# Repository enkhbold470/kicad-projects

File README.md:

# KiCad projects

Five boards, each designed end to end in KiCad 10 and checked by KiCad itself: schematic, ERC, netlist round
trip, placement, routing, pours, silkscreen, DRC with schematic parity, DFM and fab outputs. Each folder holds
the KiCad project, the gerbers / BOM / pick-and-place / STEP, raytraced renders and a video of the design
being built step by step.

<table>
<tr><td align="center" width="50%"><br><b><a href="iron-node/">Iron Node</a></b><br><sub>An ESP32-S3 industrial gateway with Ethernet, isolated RS-485, CAN and a 9-36 V input.</sub></td><td align="center" width="50%"><br><b><a href="pd-brick/">PD Brick</a></b><br><sub>A USB-C Power Delivery bench supply: STUSB4500 sink, LM5176 buck-boost, 1.2-22 V set over I2C by an ESP32-S3.</sub></td></tr>
<tr><td align="center" width="50%"><br><b><a href="probelab/">ProbeLab</a></b><br><sub>An RP2040 USB-C logic analyzer: 16 buffered 5 V-tolerant inputs plus two low-speed scope channels.</sub></td><td align="center" width="50%"><br><b><a href="spinner/">Spinner</a></b><br><sub>A 12-24 V field-oriented-control BLDC motor controller: STM32G431, three IR2104 half bridges, MT6701 encoder, CAN FD.</sub></td></tr>
<tr><td align="center" width="50%"><br><b><a href="ice-core/">Ice Core</a></b><br><sub>A 6-layer iCE40UP5K FPGA board with 8 MB PSRAM and three Pmods, programmed and clocked over USB-C by an RP2040.</sub></td></tr>
</table>

## The boards

| Board | Own repository | Layers | Size | Parts | Nets | Connections routed | Vias | DRC errors / unconnected / parity |
|---|---|---|---|---|---|---|---|---|
| [Iron Node](iron-node/) | [enkhbold470/iron-node](https://github.com/enkhbold470/iron-node) | 4 | 90 x 66 mm | 83 | 57 | 215 -> 0 | 135 | 0 / 0 / 0 |
| [PD Brick](pd-brick/) | [enkhbold470/pd-brick](https://github.com/enkhbold470/pd-brick) | 4 | 100 x 80 mm | 120 | 71 | 283 -> 0 | 208 | 0 / 0 / 0 |
| [ProbeLab](probelab/) | [enkhbold470/probelab](https://github.com/enkhbold470/probelab) | 4 | 58 x 70 mm | 88 | 84 | 253 -> 0 | 171 | 0 / 0 / 0 |
| [Spinner](spinner/) | [enkhbold470/spinner](https://github.com/enkhbold470/spinner) | 4 | 84 x 66 mm | 87 | 52 | 205 -> 0 | 167 | 0 / 0 / 0 |
| [Ice Core](ice-core/) | [enkhbold470/ice-core](https://github.com/enkhbold470/ice-core) | 6 | 80 x 60 mm | 78 | 73 | 234 -> 0 | 180 | 0 / 0 / 0 |

Every number above is read from the board's own `report.json`, written by the run that produced the files.
Each board is also published as its own repository, with unzipped gerbers in `fab/gerbers/`, for sites that
import one design per repository.

## How they were made

The boards were designed with the HeyPCB method on KiCad 10.0.6, headless: a written brief is composed from
reusable circuit blocks, every pin comes from KiCad's own symbol library, every part is bound to an LCSC
number from a dated catalogue lookup, and each stage is gated by a measurement:

```
brief -> blocks -> schematic -> ERC -> netlist round trip -> board -> placement -> Freerouting 2.4.1
      -> last-mile router -> pours + stitching (only at 0 open) -> silkscreen -> DRC + schematic parity
      -> DFM -> fab gate -> gerbers / BOM / CPL / STEP -> renders -> design-process video
```

A stage that could not measure holds the run; nothing is assumed to pass. Each board's README lists the chip
substitutions made along the way, the design decisions, and what to check before ordering.

## Status

None of these boards has been fabricated, assembled or powered, and no firmware or gateware ships with them.
They pass every check KiCad can run; they have not met a soldering iron. Part numbers and stock are dated
catalogue snapshots: re-check them before ordering.

## License

Hardware designs: [CERN-OHL-S v2](LICENSE). KiCad's symbol, footprint and 3D libraries used in the designs are
CC-BY-SA 4.0 with the KiCad library exception. 3D bodies under `kicad/models/` are simplified envelopes
generated for parts whose KiCad model is missing, not vendor models.

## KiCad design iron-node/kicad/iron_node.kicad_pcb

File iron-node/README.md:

# Iron Node

An ESP32-S3 industrial gateway with Ethernet, isolated RS-485, CAN and a 9-36 V input.

| Layers | Size | Parts | Nets | Connections routed | Vias | ERC errors | DRC errors / unconnected / parity |
|---|---|---|---|---|---|---|---|
| 4 | 90 x 66 mm | 83 | 57 | 215 -> 0 open | 135 | 0 | 0 / 0 / 0 |

**Not fabricated, assembled or powered.** Every number on this page is measured by KiCad 10 on the files in this folder; the full measurements are in [`report.json`](report.json).

| | |
|---|---|
| KiCad project | [`kicad/`](kicad/) |
| Gerbers, BOM, CPL, STEP, schematic PDF | [`fab/`](fab/) |
| Renders | [top](media/top.png), [bottom](media/bottom.png) |
| Design process, every step as KiCad rendered it | [`media/design-process.mp4`](media/design-process.mp4) |

An industrial IoT gateway: an ESP32-S3 with wired Ethernet, isolated RS-485 and CAN, powered
from a 9-36 V DC field supply or from USB-C. It was designed with the HeyPCB method on KiCad 10
(10.0.6), by heypcb-kicad's headless pipeline with Freerouting 2.4.1, from the brief in
`board.json`.

**This board has not been fabricated, assembled or powered.** Everything below is what KiCad and
the pipeline measured on the design files. Nothing here has been tested on hardware, and
nothing here contains or tests firmware.

## Specs

- **MCU:** ESP32-S3-WROOM-1-N8R8, with native USB on a USB-C port and USBLC6-2SC6 ESD
  protection. The antenna end of the module hangs 6.05 mm past the top edge (*read off the
  board*, from its F.Fab outline).
- **Ethernet:** WIZnet W5500 (LQFP-48, C32843) on SPI, with a 25 MHz crystal. It drives a HanRun
  HR911105A RJ45 MagJack (integrated 1:1 magnetics, link and activity LEDs). The circuit follows
  WIZnet's W5500-Ref-RJ45WithMag reference schematic.
- **RS-485, isolated:** ADM2587E (Analog Devices), an isolated RS-485 transceiver with its own
  isoPower DC/DC. It runs half duplex with DE/~RE on one GPIO and a pull-down. A slide switch
  fits a 120 R terminator. The bus is on a 3-pole screw terminal: A, B, isolated GND. The
  isolated side of the ADM2587E, its isoPower capacitors, the terminator, its switch and the
  terminal sit in their own corner of the board, behind a copper keep-out barrier (see
  *The isolation barrier* below).
- **CAN:** SN65HVD230 (3.3 V) with an NUP2105L bus protector. A slide switch fits a 120 R
  terminator. The bus is on a 3-pole screw terminal: CANH, CANL, GND.
- **Power:** 9-36 V DC on a 2-pole screw terminal. It goes through an SS36 series Schottky
  (reverse polarity) and an SMAJ36A TVS into an LMR36510 (TI, 4.2-65 V in, 1 A, 400 kHz,
  synchronous) that makes 3.3 V directly. USB VBUS joins the buck input through a second
  SS36, so the board also runs and flashes from USB alone. No LDO is needed: every chip on
  the board runs from 3.3 V.
- **UI:** BOOT (IO0) and RESET (EN) buttons below the module. PWR (red), RUN (orange, IO14) and
  ERR (red, IO21) LEDs, plus the jack's own link and activity LEDs.
- **Board:** 90 x 66 mm, 4 copper layers, 1.6 mm. F.Cu is signal with a GND pour, In1 a GND
  plane, In2 signal with a 3V3 pour, B.Cu signal with a GND pour, except in the isolated
  bottom-right corner, which has no pour on any layer. Four non-plated 3.2 mm holes for M3
  screws sit 4.5 mm in from the corners. USB-C is on the left edge, the RJ45 on the right edge,
  and every field terminal on the bottom edge.

### ESP32-S3 pin map

| Function | GPIO | Module pin |
|---|---|---|
| W5500 SCLK / MOSI / MISO / CS | IO41 / IO40 / IO39 / IO42 | 34 / 33 / 32 / 35 |
| W5500 INTn / RSTn | IO38 / IO2 | 31 / 38 |
| CAN TX / RX (TWAI) | IO9 / IO10 | 17 / 18 |
| RS-485 TX / RX / DE+~RE | IO11 / IO12 / IO13 | 19 / 20 / 21 |
| RUN / ERR LED | IO14 / IO21 | 22 / 23 |
| BOOT | IO0 | 27 |
| USB D- / D+ | IO19 / IO20 | 13 / 14 |

The SPI pins go through the GPIO matrix rather than the FSPI IOMUX pins, because the module's
right-side pins face the W5500. IO39-IO42 are the JTAG pins, so JTAG debugging has to go over
USB (the S3's built-in USB-JTAG). The strapping pins IO0, IO3, IO45 and IO46 carry nothing
except BOOT.

### Chip substitutions

The brief allowed swaps where a chip lacks a KiCad 10 symbol or stock. These were made:

| Asked for | Fitted | Why |
|---|---|---|
| TI ISO1410 + an isolated DC/DC (or an ISOW part) | **ADI ADM2587E** (ADM2587EBRWZ-REEL7, C12081) | The installed KiCad 10 library has no ISO1410 and no ISOW14xx symbol. TI's ISO3082/ISO3088 have symbols, but the 2026-09-30 JLC lookup found no stock for them. The ADM2587E has a stock symbol and footprint, its own isolated DC/DC, and had 5711 in stock on that date |
| TCAN1044 or SN65HVD230 | **SN65HVD230DR** (C12084) | The library has no TCAN1044 symbol, only the 14-pin TCAN1043 |
| a stocked TI/MPS synchronous buck to 5 V or 3.3 V, plus an LDO/buck to 3.3 V as needed | **LMR36510ADDAR** (C1858393) to 3.3 V, no second stage | A 65 V synchronous buck in the library with JLC stock. With USB OR-ed into its input, a single 3.3 V rail serves every chip |
| RJ45 MagJack with integrated magnetics, JLC-stocked, with a KiCad 10 footprint | **HanRun HR911105A** (C12074) | It has a stock KiCad symbol and footprint |

## The isolation barrier

The pour stage floods the whole outline: GND on F.Cu, In1 and B.Cu, 3V3 on In2. Until this build,
those pours ran under the ADM2587E, between its logic-side and isolated-side pin rows, on all four
layers. On the previous build the isolated copper came within 0.250 mm of them on every layer
(*read off* that board), and the isolated nets also ran on In2, inside the 3V3 pour. The barrier is now built from the brief's `board.keepouts`, which become KiCad
rule areas at the board stage. Coordinates are in mm from the board's top-left corner.

- **The barrier strip** (`iso_barrier_under_u6`, x 56.5-90, y 40.5-47.5) bans pours, tracks and
  vias on all four layers. It lies between the ADM2587E's two pad rows and runs to the right edge.
  The rows' pad edges are at y 40.375 and 47.625, a 7.25 mm land gap (*read off the board*). The
  strip is 7.0 mm wide and leaves 0.125 mm to each row.
- **The barrier's leg** (`iso_barrier_down`, x 56.5-63.5, y 40.5-66) has the same bans. It runs
  from the strip down to the bottom edge, between the CAN and RS-485 terminals. With the board
  edges, the strip and the leg close off the bottom-right corner.
- **The isolated region** (`iso_region_no_pour`, x 63.5-90, y 47.5-66, 26.5 x 18.5 mm) bans pours
  only. No GND or 3V3 pour enters it on any layer, and the isolated nets route there as tracks.
  The rule area is withheld from Freerouting. No stitching via lands there either, because a
  stitching via needs GND fill on every GND layer.
- **Placement.** The ADM2587E, its three isolated-side capacitors (C32-C34), the 120 R terminator
  (R18), its switch (SW2) and the terminal (J5) are locked into the region. The barrier and the
  region are placement reserves, so the placer keeps every other part out of them.
- **Net class.** The isolated nets (ISO_GND, ISO_3V3, RS485_A, RS485_B, RS485_TERM) form the ISO
  class, with 0.5 mm clearance between each other and 0.2 mm tracks.

*Read off the board* with KiCad 10.0.6's `pcbnew` on the final `kicad/iron_node.kicad_pcb`. This
is the minimum edge-to-edge distance between copper of an isolated net and copper of any other
net: pads, plated hole walls, tracks, vias and pour fills. Two methods were used (exact segment
distances, and a bisection on inflated polygons), and they agree.

| Layer | Isolated copper to other copper | Where |
|---|---|---|
| F.Cu | **7.125 mm** | ISO_GND pad U6.11 to the GND pour that fills from GND pad U6.10 down to the strip's edge |
| In1.Cu | 8.371 mm | an ISO_GND via at (65.17, 49.59) to the GND plane at the leg's edge |
| In2.Cu | 8.371 mm | the same via to the 3V3 pour at the leg's edge |
| B.Cu | 8.371 mm | the same via to the GND pour at the leg's edge |
| any layer to any layer, in plan view | **7.125 mm** | the same F.Cu pair; no copper overlaps across layers |

- The unnetted copper inside the region does not lower the number when it is counted with the
  isolated side. That copper is the PCM12's shell pads and its unused throw.
- Every isolated track and via lies inside the region, and no other net's track or via ends in the
  region or the barrier. The isolated nets have 142.0 mm of track (F.Cu 96.5, In2 45.4, none on
  B.Cu) and 6 vias. ISO_GND is routed as tracks: 46.1 mm, 4 vias.
- At the package, no copper keep-out can beat the footprint's 7.25 mm land gap; only a slot
  could. The strip stops 0.125 mm short of each pad row, which is where 7.125 mm comes from.
  This board has no slot.
- **Clearance is not a rating.** The ADM2587E's 2.5 kV rms is a rating of the part. The board
  provides the distances above. The board has no slot, so on each outer face the shortest surface
  path across the barrier is the straight line measured on that face. Whether 7.125 mm is enough
  depends on the working voltage, the pollution degree, the material group and the standard the
  product is assessed to. None of that was assessed here.

## What it measured

A full run with media on 2026-10-01 (KiCad 10.0.6, Freerouting 2.4.1). Gate numbers are from
`report.json`. Anything marked *read off the board* was measured on `kicad/iron_node.kicad_pcb`
with KiCad 10.0.6's `pcbnew` Python module. That file's SHA-256 is the board hash DRC recorded.

| Gate | Result |
|---|---|
| Composition | 83 parts, 57 nets, 43 no-connects (16 block instances of 11 distinct blocks, 5 of them new `iron_*` blocks) |
| Part binding | 79 of 83 parts bound to an LCSC number, 0 unsourced, 0 identity conflicts. H1-H4, the mounting holes, are not BOM parts. 19 distinct Extended parts, about $57 in JLC loading fees. 3 warnings: R5, R15 and R17 use the 10k 0603 C25804, which had 0 stock at its 2026-06-23 snapshot |
| ERC (`kicad-cli sch erc --severity-all`) | 0 errors, 0 warnings |
| Netlist round trip | identical, 57 nets |
| Routing, rung 1, fanout on | Freerouting left 1 of 215 connections open (VBUS, J2.A9 to C9.1). The last-mile router closed it (3 tracks, 1 via, 0.08 s), and DRC accepted it with no new error. 23.6 s, 70 vias. **This solve is kept** |
| Routing, rung 1, fanout off | Freerouting left 2 open. The last mile closed VBUS and found no path for ISO_GND (U6.16 to C32.2), so 1 stayed open. 23.0 s, 70 vias |
| Net classes | No class was narrowed. Every track is at its class width (*read off the board*): PWR 98.4 mm at 0.5 mm, ISO 142.0 mm at 0.2 mm, everything else 1667.7 mm at 0.2 mm |
| Copper | 730 tracks, 1908.0 mm (F.Cu 1058.5, In2 766.2, B.Cu 83.3), 70 routing vias |
| Pours (laid only after a measured 0 open) | GND on F.Cu, In1 and B.Cu, 3V3 on In2, kept out of the barrier and the isolated region. Then 72 stitching vias, 142 vias in total. 0 open after the pours and after stitching, 0 island-repair vias |
| Silkscreen | 16 words placed (see *Silkscreen labels* below), 47 designators seated and 24 hidden, all 5 back-side title lines placed. The text displaced 7 stitching vias, which leaves 135 vias on the board (*read off the board*, all 0.6/0.3 mm). 22 footprint silk strokes that left the board or came within 0.3 mm of its edge were dropped |
| DRC (`kicad-cli pcb drc --severity-all --schematic-parity`) | fresh (its board hash matches the final `.kicad_pcb`), 0 errors, 0 unconnected, 0 parity issues, 5 warnings |
| DFM (`jlcpcb_4layer` profile) | 0 errors, 1 warning: 255 stock-footprint silk strokes at 0.12 mm, which the fab prints at its 0.15 mm minimum |
| Fab gate | ready, no blockers. 4 copper gerbers and a gerber job with LayerNumber 4, 1.6 mm. The JLC CPL corrected 5 rotations |
| 3D, renders, video | all ran: 63 3D frames, then the renders (171.1 s) and the design-process video (214 frames, 146.4 s at 1920 x 1080, measured with ffprobe) |

- **The 5 DRC warnings** are all `lib_footprint_mismatch`: J1, J4 and J5 (the screw terminals),
  J2 (USB-C) and U3 (the module). These are the five footprints that lost silk strokes at the
  board edge (*read off the board* against the library: 5 each on J1, J4 and J5, 4 on U3, 3 on
  J2). J1-J5 also carry a generated 3D body from `kicad/models/`. J3 carries one too and is not
  flagged, so the flag follows the dropped strokes.
- The project's DRC settings ignore five checks: missing courtyard, track not centred on via,
  tuning-profile track geometry, footprint filters mismatch and footprint type mismatch.

### Why the brief looks the way it does

These were measured on runs from 2026-09-30 to 2026-10-01. The reasons are also recorded in
`board.json`.

- **Screw terminals are locked, not edge-placed.** The placer's edge rung tests which side of a
  connector is its mouth. It picked the back of the MX126 terminals, because their pins sit
  mid-body (4.0 mm to the back face, 3.8 mm to the front). They are locked at rot 0 with the pins
  3.8 mm in from the bottom edge. KiCad's footprint generator draws the wire entry on local +y.
  This was checked against the Phoenix MKDS footprint, which has the same drawing and a 3D model.
- **The ISO class has 0.5 mm clearance and 0.2 mm tracks.** Its clearance used to be held at the
  board's 0.2 mm, because a GND stitching via landed 0.35 mm from an ISO_GND track. Now the
  stitcher and the pours stay out of the isolated region, so the class takes its own clearance.
  0.5 mm is the most the region's footprints allow: the ADM2587E's pads are 0.67 mm apart, and the
  PCM12's B throw is 0.55 mm from its own mounting pad. At 0.3 mm tracks, all four rung-1 solves
  over two runs left one isolated connection open: ISO_GND U6.16-C32.2 or RS485_B U6.15-J5.2. The
  ladder's narrowing to 0.2 mm then routed them all. The bus and the isoPower supply carry tens of
  mA.
- **In2 is a routing layer, not a GND plane.** A plane layer goes to Freerouting as a power
  layer. A run with In2 named a GND plane routed on F.Cu and B.Cu only and left ISO_GND open. In2
  routes, then takes the 3V3 pour.
- **3V3 has no net class of its own.** In four earlier runs with a 0.3 mm 3V3 class, the routing
  ladder had to narrow it to 0.2 mm every time. 3V3 now routes at 0.2 mm (237.0 mm of track,
  *read off the board*), and the In2 3V3 pour carries its current.
- **The buttons sit below the module.** A silk word may not overlap any courtyard. The module's
  courtyard box covers x -2 to 46 down to y 20.25, and the USB-C receptacle's starts at y 21.64.
  At their old spots (BOOT at (37, 16), RESET at (6, 14.5), then at (6, 18.5)), neither a word nor
  a designator fit. BOOT is now at (37, 19.5), with its word below it, and RESET at (29, 30), with
  its word beside it.
- **J1's + and - are switch words.** `silk.polarity` puts its mark 1.9-2.3 mm from the pad centre,
  which is inside a 2.8 mm terminal pad's own clearance. So it never placed J1's marks. The brief
  instead gives J1 a `silk.switches` entry keyed on each pin's net. That places "+" above pin 1
  (VIN_RAW) and "-" above pin 2 (GND), just beyond the terminal's courtyard.

## Check before ordering

The board passes ERC, DRC with schematic parity, DFM and the fab gate in KiCad. **It has not been
fabricated, assembled or powered.**

- **The RS-485 isolation is measured, not rated.** The barrier above gives 7.125 mm on F.Cu, at
  the ADM2587E's own pad rows, and 8.371 mm on the other layers. Check those distances against the
  working voltage and the standard the product must meet. To gain more at the package, cut a slot
  in the barrier strip between the pad rows (not done here).
- **The bottom-right M3 hole (H4) is inside the isolated region.** It is non-plated, with no net.
  Its hole edge is 4.34 mm from the nearest isolated copper (SW2's B throw) and 2.77 mm from
  SW2's unnetted shell pad (*read off the board*). A metal screw or standoff there is a conductor
  in the isolated region. Use a nylon screw, or check its head and standoff against the isolated
  copper and the enclosure.
- **The isolated region has no ground pour.** ISO_GND is a 0.2 mm track (46.1 mm on F.Cu and In2,
  4 vias). The brief has no key for a pour of one net inside one region (`board.pours` takes a
  whole inner layer). If EMC or surge testing asks for an ISO_GND plane, add it in KiCad.
- **Power traces run on In2.** *Read off the board:* VIN_RAW, VIN, VBUS and BUCK_SW are 0.5 mm
  along their whole length. VIN (25.3 mm) and BUCK_SW (8.9 mm) are on F.Cu. VBUS is 44.9 mm with
  4 vias, 25.3 mm of it on In2. VIN_RAW is 19.3 mm with 1 via, 17.3 mm of it on In2. The gerber
  job states 0.035 mm copper on every layer, which is KiCad's default stackup, not a fab quote.
  Confirm the inner-layer copper weight with the fab against the input and VBUS current (the buck
  is a 1 A part), or move those two nets to an outer layer.
- **Screw-terminal orientation.** The MX126 wire entry is taken to be on the footprint's +y side.
  That is KiCad's generator convention, checked on the Phoenix MKDS model. KiCad 10.0.6 installs
  no MaiXu model. The bodies in `kicad/models/` are generated from the footprint outline, with the
  openings on +y and a 10 mm height envelope, so the renders show the assumption, not a check.
  Confirm against MaiXu's drawing that the openings face out of the bottom edge.
- **Running from USB alone.** VIN is VBUS minus an SS36 drop, about 4.5 V, against the LMR36510's
  4.2 V minimum. That is enough to flash and run the MCU, but run the RS-485 isoPower at full load
  and Wi-Fi from the field supply. A default USB port gives only 500 mA.
- **3.3 V setpoint.** RFBT/RFBB are 47k/20k (both Basic parts), so VOUT = 1.0 V x (1 + 47/20) =
  3.35 V nominal, against TI's 100k/43.2k for 3.3 V. Every chip on the rail is specified to 3.6 V.
- **No input fuse.** Reverse polarity is a series SS36, and surge is an SMAJ36A after it. A
  sustained overvoltage above the TVS rating will short the TVS. Add a fuse or PTC for a field
  installation.
- **Crystal load.** The JLC mirror lists the X322525MOB4SI (C9006) as a 12 pF load part. The
  18 pF caps follow WIZnet's reference. Measure the 25 MHz error on a first article and trim the
  caps if needed (Ethernet allows +/-50 ppm).
- **Ethernet layout.** Freerouting routed the MDI lines with no impedance control or length
  matching. *Read off the board*, as track per net with the stubs to the terminations included:
  ETH_TXP is 14.9 mm and ETH_TXN 13.2 mm, with one via each. On the receive side, through the
  6.8 nF coupling caps, RD+ is 24.5 mm with 4 vias and RD- is 27.5 mm with 1 via. WIZnet's
  optional VDD/AVDD ferrite and 33 R damping resistors are not fitted. The W5500 has no Auto-MDIX.
- **USB.** *Read off the board:* D+ is 34.1 mm and D- 30.2 mm, both on F.Cu with no via. Both are
  0.2 mm with no impedance control. That is fine for the S3's Full Speed USB.
- **Part numbers.** The rows this board added were read live from jlcsearch on 2026-09-30 and
  pinned with that date. Stock and Basic/Extended class go stale, so re-check before ordering. On
  that date LMR36510ADDAR had 1663 in stock and ADM2587EBRWZ-REEL7 had 5711. R5, R15 and R17
  bind to the 10k 0603 C25804, which had 0 stock at its 2026-06-23 snapshot, so pick a stocked
  10k.
- **Grounds.** The M3 holes are non-plated with no net (*read off the board*), so the enclosure is
  not bonded to any ground. The RJ45 shield reaches GND only through 1 nF / 2 kV. CAN is not
  isolated: its terminal GND is the board GND.
- **Debug.** IO39-IO42 carry the W5500's SPI, so JTAG is available over USB only.
- **Silkscreen labels.** *Read off the board:* the front carries USB, ETH, 9-36V, CAN, RS-485,
  PWR, RUN, ERR, BOOT and RST. A "+" sits above J1's pin 1 and a "-" above its pin 2. Each
  termination switch has a 120R and an OFF word, each level with the throw it names. The CAN and
  RS-485 terminals have no per-pin marks on the front. Their pinouts are on the back ("CAN: 1 H 2
  L 3 GND  RS-485: 1 A 2 B 3 GISO"), with "IN: 1 +9..36V 2 GND", "ESP32-S3 / W5500 / iso RS-485 /
  CAN" and "rev A heypcb-kicad NOT FABRICATED" under the "Iron Node" title. 24 designators found
  no free spot and are hidden.
- **Termination switch labels.** SW2 (RS-485) is turned with its slider toward the right edge. Its
  120R sits left of throw 1 (B), and its OFF sits left of throw 3. SW1 (CAN) has 120R below
  throw 1 (CAN_L) and OFF above throw 3, each in line with its throw. Both labels assume that the
  PCM12 joins its common pin to the throw on the side the slider is pushed toward. Check that
  against C&K's drawing.

## Files

- `board.json`: the brief. It lists the blocks, net classes, keep-outs, placement targets, routing
  and silk settings, each with its reason.
- `report.json`: the run's gate report. Every gate number above comes from it.
- `kicad/`: `iron_node.kicad_pro`, `iron_node.kicad_sch` and the routed, poured
  `iron_node.kicad_pcb`. `kicad/models/` holds generated simplified bodies for the USB-C
  receptacle, the RJ45 and the 2- and 3-pole MX126 terminals. They are VRML envelopes, not vendor
  models.
- `fab/iron_node_gerbers.zip`: 11 gerbers (4 of them copper), the gerber job, the drill file
  and the drill map.
- `fab/iron_node_bom.csv`: the BOM, with MPN and LCSC columns.
- `fab/iron_node_cpl_jlc.csv` and `fab/iron_node_pos.csv`: the JLC CPL and KiCad's position file.
  Each lists 75 parts. The through-hole J1, J3, J4 and J5 are not in them.
- `fab/iron_node_schematic.pdf`: the schematic.
- `fab/iron_node.step`: the 3D model. It has no body for J1-J5, because their generated bodies are
  VRML, which the STEP export did not include.
- `media/`: `hero.png`, `top.png` and `bottom.png` are KiCad renders, and
  `design-process.mp4` and `design-process.gif` show the pipeline's stages. The USB-C, RJ45 and
  terminal bodies in the renders are the generated envelopes.

In the heypcb-kicad repository, `./run.sh --board boards/iron_node` regenerates these outputs
from `board.json`. The
five blocks written for this board (`iron_power_lmr36510`, `iron_w5500_ethernet`,
`iron_rs485_adm2587e`, `iron_can_sn65hvd230` and `iron_mounting_hole_m3`) give, in their notes,
the symbol pinout each was wired from and the data sheet or reference design its values came from.

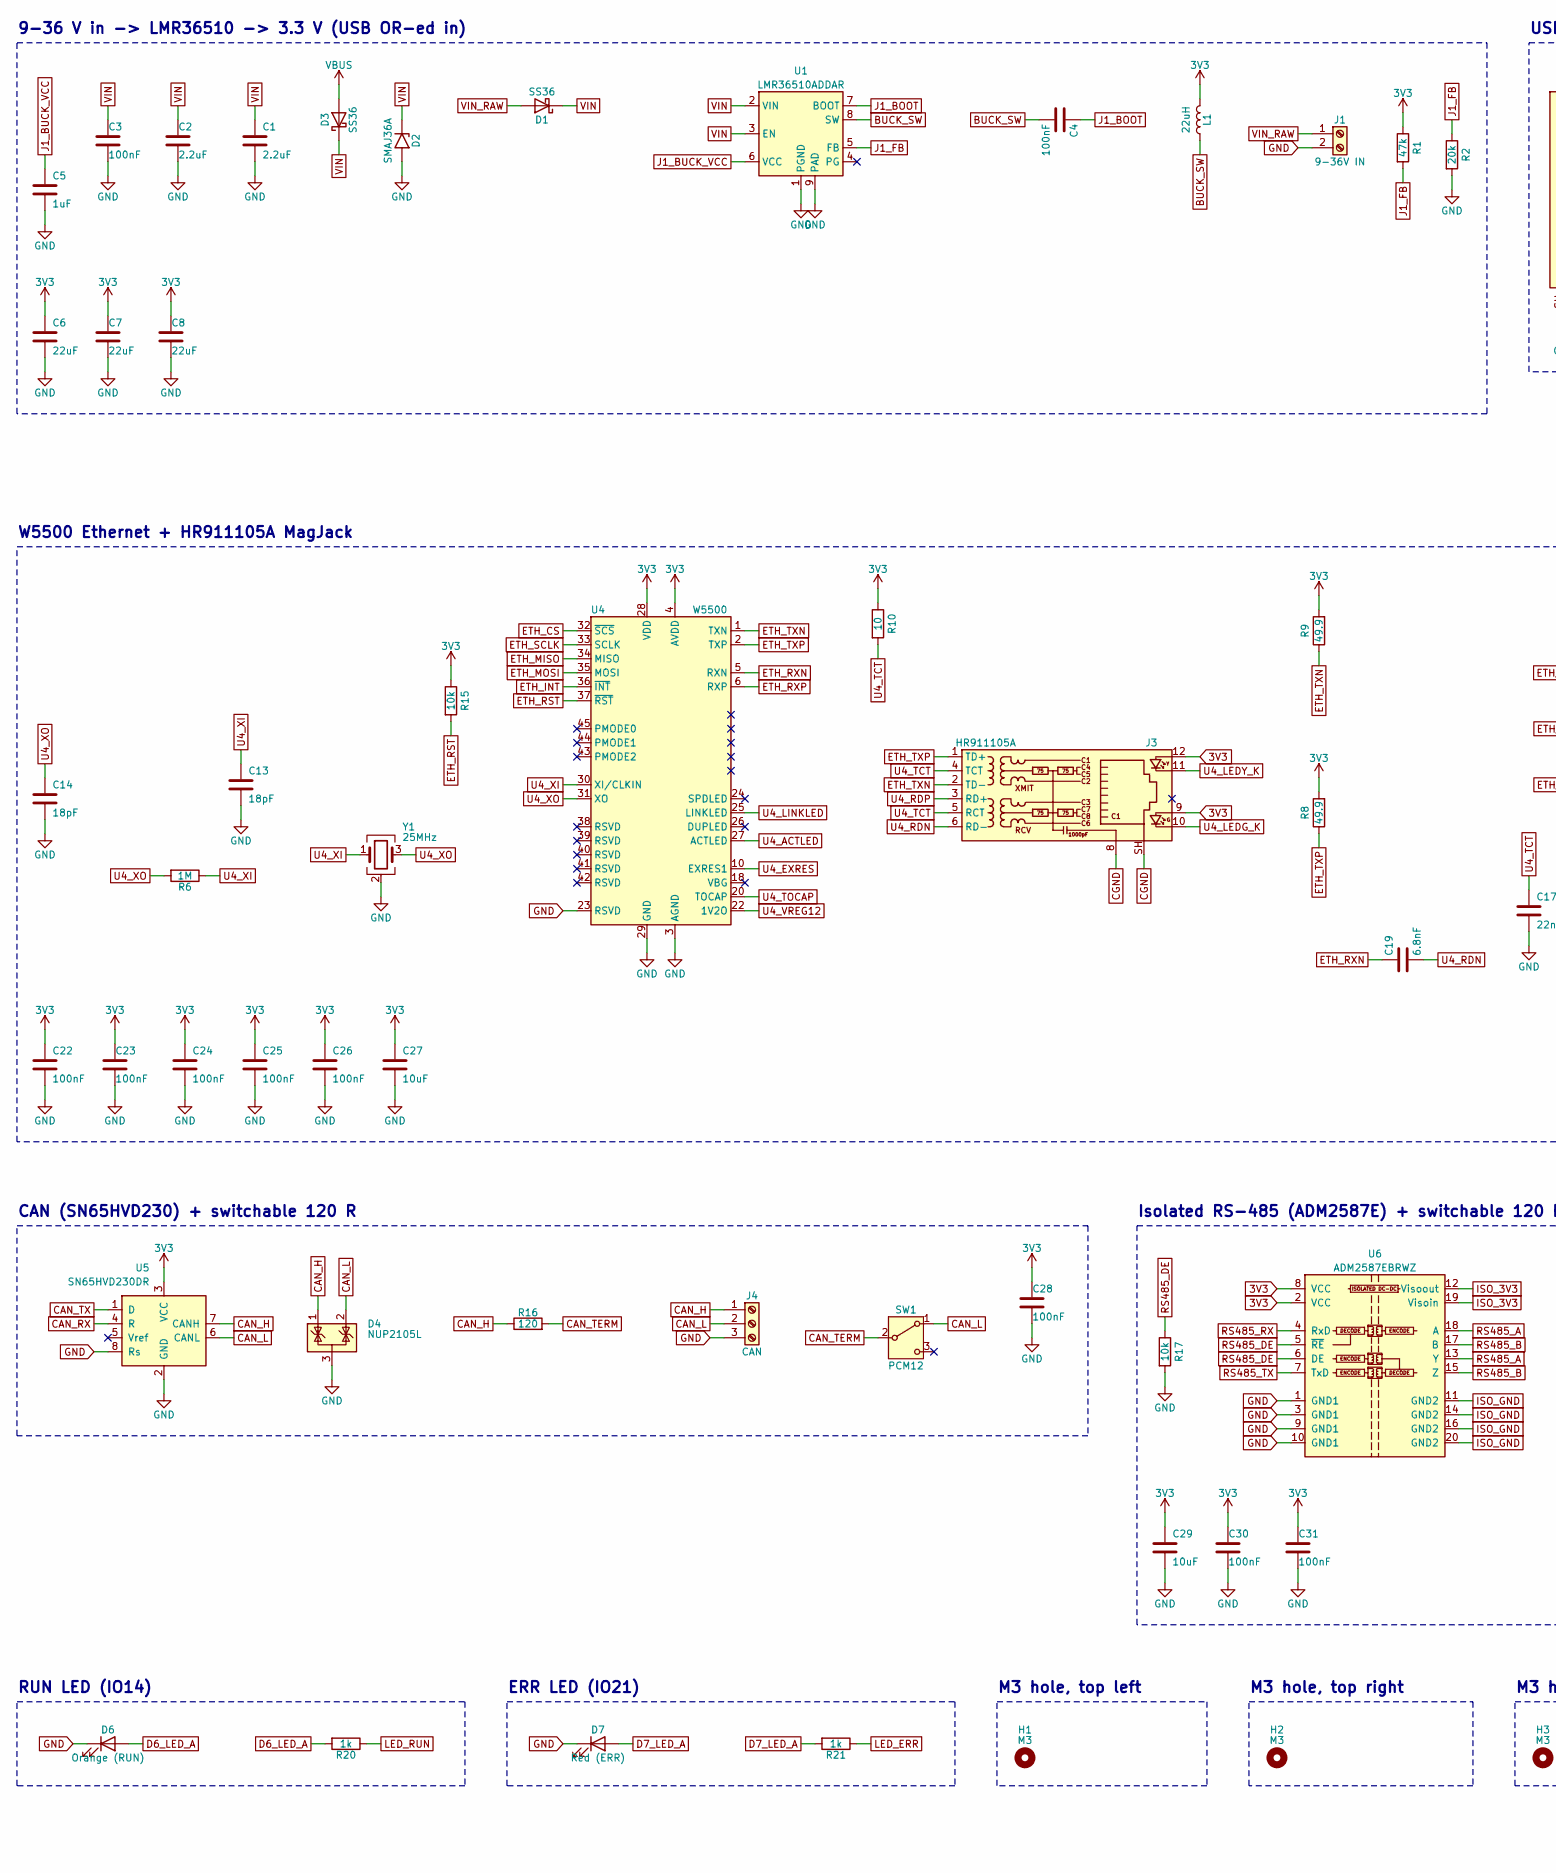
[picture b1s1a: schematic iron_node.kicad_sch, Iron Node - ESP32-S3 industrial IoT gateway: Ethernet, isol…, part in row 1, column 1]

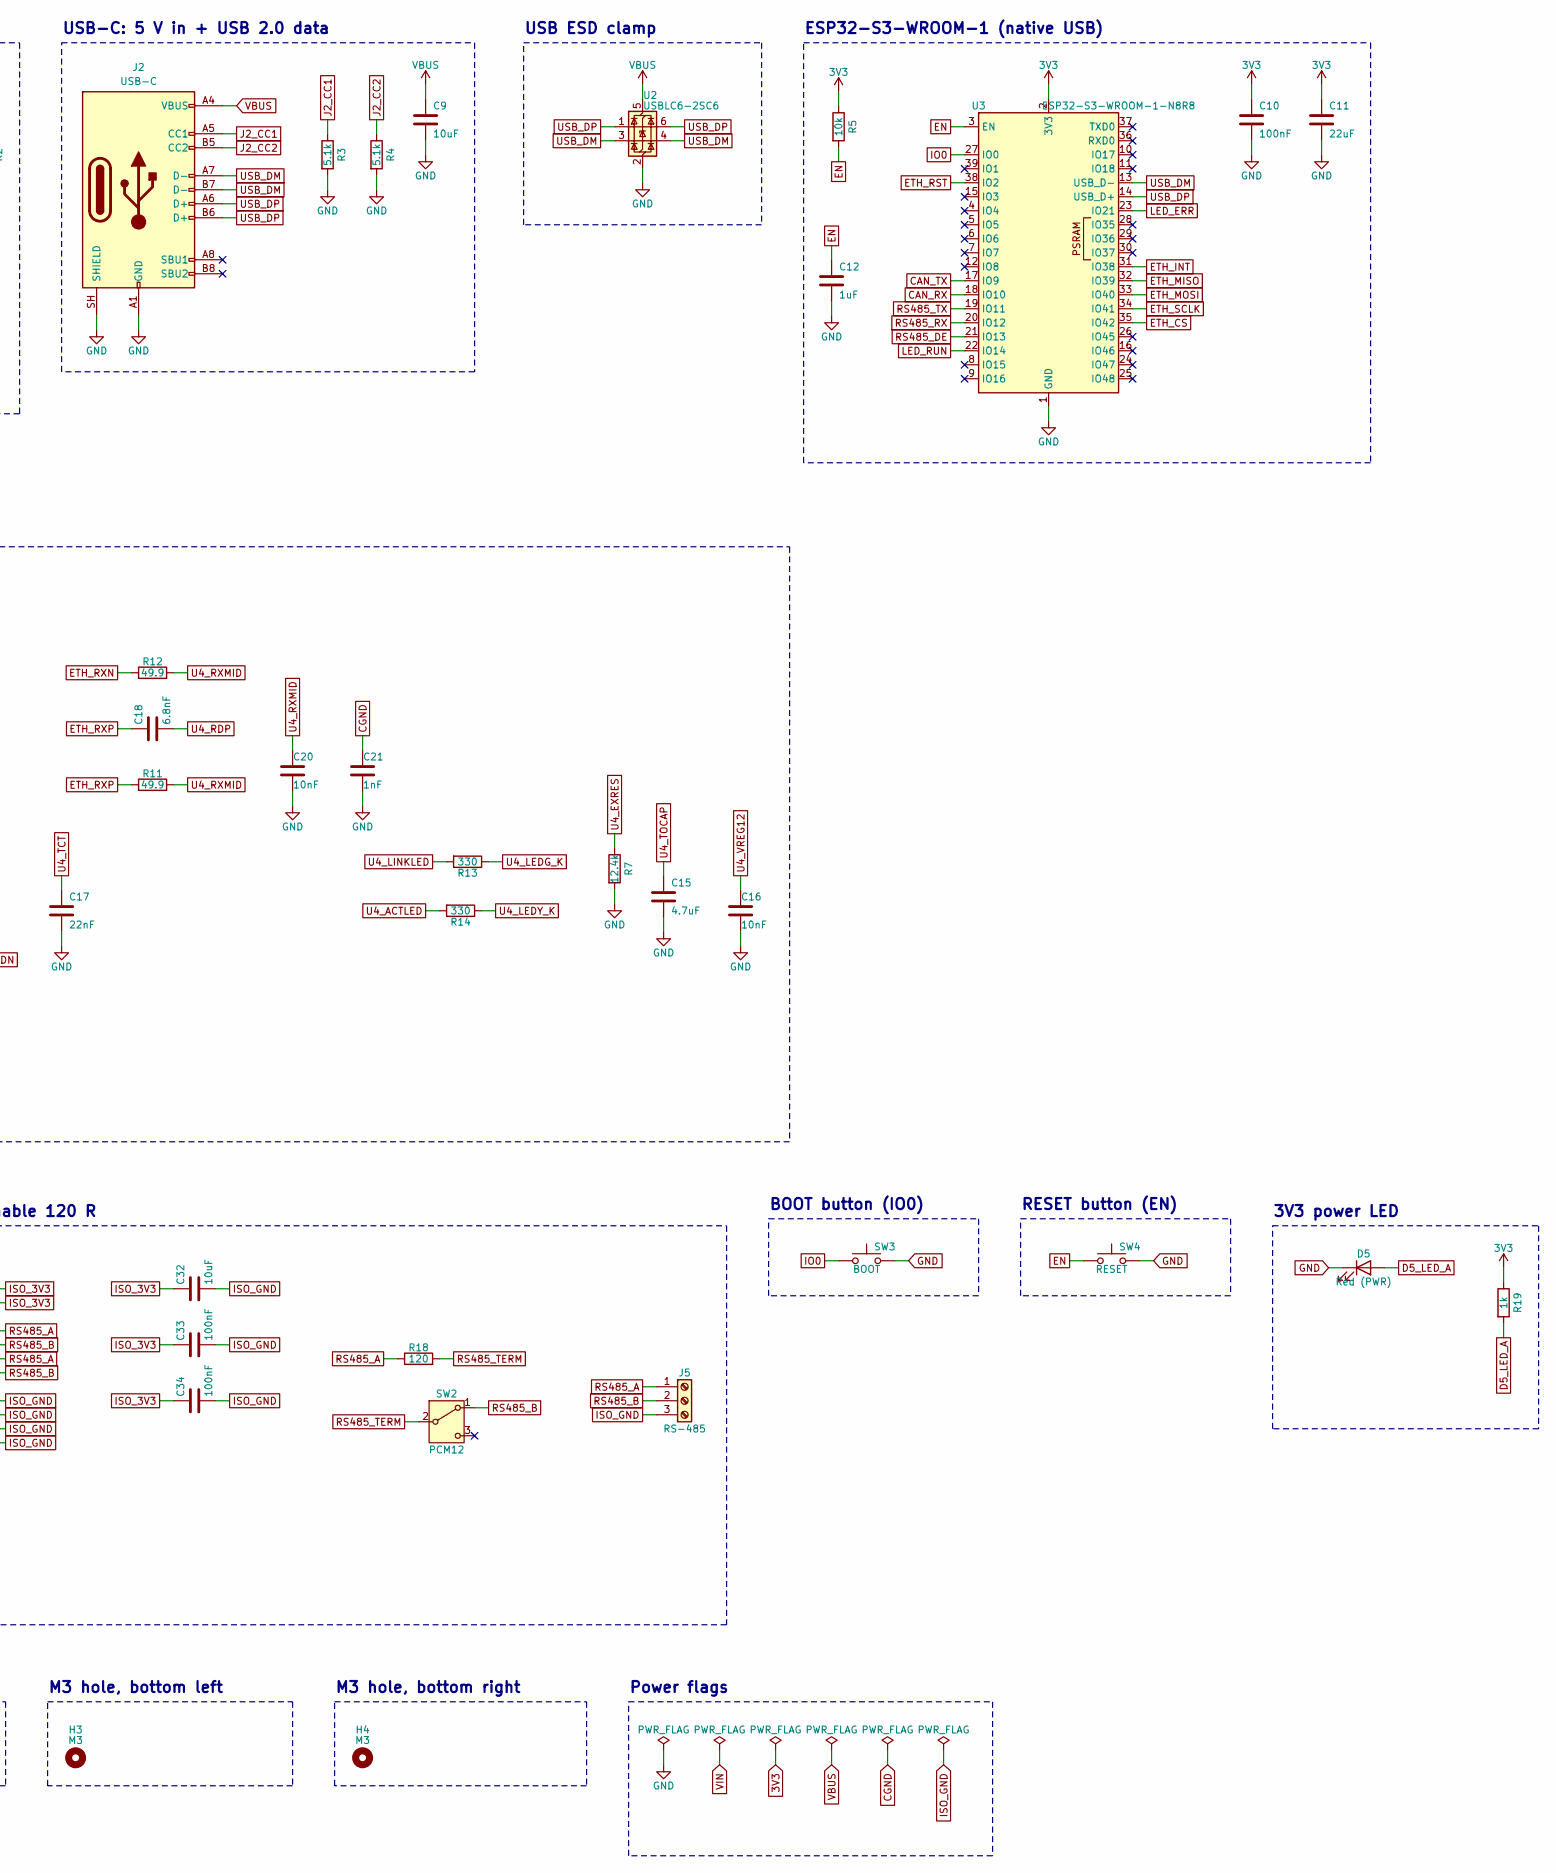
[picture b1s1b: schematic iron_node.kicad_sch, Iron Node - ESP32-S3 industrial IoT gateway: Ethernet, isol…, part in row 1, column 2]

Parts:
C1, C2: 2.2uF; C_1210_3225Metric; MPN FS32X225K101EGG; LCSC C153036
C3: 100nF; C_0805_2012Metric; MPN CL21B104KCFNNNE; LCSC C28233
C4, C10, C22, C23, C24, C25, C26, C28, C30, C31, C33, C34: 100nF; C_0603_1608Metric; MPN CC0603KRX7R9BB104; LCSC C14663
C5, C12: 1uF; C_0603_1608Metric; MPN CL10A105KB8NNNC; LCSC C15849
C6, C7, C8, C11: 22uF; C_0805_2012Metric; MPN CL21A226MAQNNNE; LCSC C45783
C9, C27, C29, C32: 10uF; C_0805_2012Metric; MPN CL21A106KAYNNNE; LCSC C15850
C13, C14: 18pF; C_0603_1608Metric; MPN CL10C180JB8NNNC; LCSC C1647
C15: 4.7uF; C_0805_2012Metric; MPN CL21A475KAQNNNE; LCSC C1779
C16, C20: 10nF; C_0603_1608Metric; MPN 0603B103K500NT; LCSC C57112
C17: 22nF; C_0603_1608Metric; MPN CL10B223KB8NNNC; LCSC C21122
C18, C19: 6.8nF; C_0603_1608Metric; MPN 0603B682K500NT; LCSC C1631
C21: 1nF; C_1206_3216Metric; MPN 1206B102K202NT; LCSC C9196
D1, D3: SS36; D_SMA; MPN SS36; LCSC C16015
D2: SMAJ36A; D_SMA; MPN SMAJ36A; LCSC C113967
D4: NUP2105L; SOT-23; MPN NUP2105LT1G; LCSC C14486
D5: Red (PWR); LED_0603_1608Metric; MPN KT-0603R; LCSC C2286
D6: Orange (RUN); LED_0603_1608Metric; MPN XL-1608UOC-06; LCSC C965800
D7: Red (ERR); LED_0603_1608Metric; MPN KT-0603R; LCSC C2286
H1, H2, H3, H4: M3; MountingHole_3.2mm_M3
J1: 9-36V IN; TerminalBlock_MaiXu_MX126-5.0-02P_1x02_P5.00mm; MPN MX126-5.0-02P-GN01-Cu-S-A; LCSC C5188434
J2: USB-C; USB_C_Receptacle_HRO_TYPE-C-31-M-12; MPN TYPE-C-31-M-12; LCSC C165948
J3: HR911105A; RJ45_Hanrun_HR911105A_Horizontal; MPN HR911105A; LCSC C12074
J4: CAN; TerminalBlock_MaiXu_MX126-5.0-03P_1x03_P5.00mm; MPN MX126-5.0-03P-GN01-Cu-S-A; LCSC C5188435
J5: RS-485; TerminalBlock_MaiXu_MX126-5.0-03P_1x03_P5.00mm; MPN MX126-5.0-03P-GN01-Cu-S-A; LCSC C5188435
L1: 22uH; L_Sunlord_SWPA6045S; MPN SWPA6045S220MT; LCSC C83454
R1: 47k; R_0603_1608Metric; MPN 0603WAF4702T5E; LCSC C25819
R2: 20k; R_0603_1608Metric; MPN 0603WAF2002T5E; LCSC C4184
R3, R4: 5.1k; R_0402_1005Metric; MPN 0402WGF5101TCE; LCSC C25905
R5, R15, R17: 10k; R_0603_1608Metric; MPN 0603WAF1002T5E; LCSC C25804
R6: 1M; R_0603_1608Metric; MPN 0603WAF1004T5E; LCSC C22935
R7: 12.4k; R_0603_1608Metric; MPN FRC0603F1242TS; LCSC C2930060
R8, R9, R11, R12: 49.9; R_0603_1608Metric; MPN 0603WAF499JT5E; LCSC C23185
R10: 10; R_0603_1608Metric; MPN 0603WAF100JT5E; LCSC C22859
R13, R14: 330; R_0603_1608Metric; MPN 0603WAF3300T5E; LCSC C23138
R16, R18: 120; R_0603_1608Metric; MPN 0603WAF1200T5E; LCSC C22787
R19, R20, R21: 1k; R_0603_1608Metric; MPN 0603WAF1001T5E; LCSC C21190
SW1, SW2: PCM12; SW_SPDT_PCM12; MPN PCM12SMTR; LCSC C221841
SW3: BOOT; SW_SPST_PTS810; MPN PTS810SJM250SMTRLFS; LCSC C116501
SW4: RESET; SW_SPST_PTS810; MPN PTS810SJM250SMTRLFS; LCSC C116501
U1: LMR36510ADDAR; Texas_HTSOP-8-1EP_3.9x4.9mm_P1.27mm_EP2.95x4.9mm_Mask2.4x3.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; MPN LMR36510ADDAR; LCSC C1858393
U2: USBLC6-2SC6; SOT-23-6; MPN USBLC6-2SC6; LCSC C7519
U3: ESP32-S3-WROOM-1-N8R8; ESP32-S3-WROOM-1; MPN ESP32-S3-WROOM-1-N8R8; LCSC C2913201
U4: W5500; LQFP-48_7x7mm_P0.5mm; MPN W5500; LCSC C32843
U5: SN65HVD230DR; SOIC-8_3.9x4.9mm_P1.27mm; MPN SN65HVD230DR; LCSC C12084
U6: ADM2587EBRWZ; SOIC-20W_7.5x12.8mm_P1.27mm; MPN ADM2587EBRWZ-REEL7; LCSC C12081
Y1: 25MHz; Crystal_SMD_3225-4Pin_3.2x2.5mm; MPN X322525MOB4SI; LCSC C9006

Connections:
3V3: C6.1, C7.1, C8.1, C10.1, C11.1, C22.1, C23.1, C24.1, C25.1, C26.1, C27.1, C28.1, C29.1, C30.1, C31.1, J3.9, J3.12, L1.2, R1.1, R5.1, R8.2, R9.2, R10.1, R15.1, R19.1, U3.2 (3V3), U4.4 (AVDD), U4.8 (AVDD), U4.11 (AVDD), U4.15 (AVDD), U4.17 (AVDD), U4.21 (AVDD), U4.28 (VDD), U5.3 (VCC), U6.2 (VCC), U6.8 (VCC)
BUCK_SW: C4.2, L1.1, U1.8 (SW)
CAN_H: D4.1 (K), J4.1, R16.1, U5.7 (CANH)
CAN_L: D4.2 (K), J4.2, SW1.1 (A), U5.6 (CANL)
CAN_RX: U3.18 (IO10), U5.4 (R)
CAN_TERM: R16.2, SW1.2 (B)
CAN_TX: U3.17 (IO9), U5.1 (D)
CGND: C21.1, J3.8, J3.SH
D5_LED_A: D5.2 (A), R19.2
D6_LED_A: D6.2 (A), R20.2
D7_LED_A: D7.2 (A), R21.2
EN: C12.1, R5.2, SW4.1, U3.3 (EN)
ETH_CS: U3.35 (IO42), U4.32 (~SCS)
ETH_INT: U3.31 (IO38), U4.36 (~INT)
ETH_MISO: U3.32 (IO39), U4.34 (MISO)
ETH_MOSI: U3.33 (IO40), U4.35 (MOSI)
ETH_RST: R15.2, U3.38 (IO2), U4.37 (~RST)
ETH_RXN: C19.1, R12.1, U4.5 (RXN)
ETH_RXP: C18.1, R11.1, U4.6 (RXP)
ETH_SCLK: U3.34 (IO41), U4.33 (SCLK)
ETH_TXN: J3.2 (TD-), R9.1, U4.1 (TXN)
ETH_TXP: J3.1 (TD+), R8.1, U4.2 (TXP)
GND: C1.2, C2.2, C3.2, C5.2, C6.2, C7.2, C8.2, C9.2, C10.2, C11.2, C12.2, C13.2, C14.2, C15.2, C16.2, C17.2, C20.2, C21.2, C22.2, C23.2, C24.2, C25.2, C26.2, C27.2, C28.2, C29.2, C30.2, C31.2, D2.2 (A2), D4.3 (A), D5.1 (K), D6.1 (K), D7.1 (K), J1.2, J2.A1 (GND), J2.A12 (GND), J2.B1 (GND), J2.B12 (GND), J2.SH (SHIELD), J4.3, R2.2, R3.2, R4.2, R7.2, R17.2, SW3.2, SW4.2, U1.1 (PGND), U1.9 (PAD), U2.2 (GND), U3.1 (GND), U3.40 (GND), U3.41 (GND), U4.3 (AGND), U4.9 (AGND), U4.14 (AGND), U4.16 (AGND), U4.19 (AGND), U4.23 (RSVD), U4.29 (GND), U4.48 (AGND), U5.2 (GND), U5.8 (Rs), U6.1 (GND1), U6.3 (GND1), U6.9 (GND1), U6.10 (GND1), Y1.2 (G), Y1.4 (G)
IO0: SW3.1, U3.27 (IO0)
ISO_3V3: C32.1, C33.1, C34.1, U6.12 (Visoout), U6.19 (Visoin)
ISO_GND: C32.2, C33.2, C34.2, J5.3, U6.11 (GND2), U6.14 (GND2), U6.16 (GND2), U6.20 (GND2)
J1_BOOT: C4.1, U1.7 (BOOT)
J1_BUCK_VCC: C5.1, U1.6 (VCC)
J1_FB: R1.2, R2.1, U1.5 (FB)
J2_CC1: J2.A5 (CC1), R3.1
J2_CC2: J2.B5 (CC2), R4.1
LED_ERR: R21.1, U3.23 (IO21)
LED_RUN: R20.1, U3.22 (IO14)
RS485_A: J5.1, R18.1, U6.13 (Y), U6.18 (A)
RS485_B: J5.2, SW2.1 (A), U6.15 (Z), U6.17 (B)
RS485_DE: R17.1, U3.21 (IO13), U6.5 (~RE), U6.6 (DE)
RS485_RX: U3.20 (IO12), U6.4 (RxD)
RS485_TERM: R18.2, SW2.2 (B)
RS485_TX: U3.19 (IO11), U6.7 (TxD)
U4_ACTLED: R14.2, U4.27 (ACTLED)
U4_EXRES: R7.1, U4.10 (EXRES1)
U4_LEDG_K: J3.10, R13.1
U4_LEDY_K: J3.11, R14.1
U4_LINKLED: R13.2, U4.25 (LINKLED)
U4_RDN: C19.2, J3.6 (RD-)
U4_RDP: C18.2, J3.3 (RD+)
U4_RXMID: C20.1, R11.2, R12.2
U4_TCT: C17.1, J3.4 (TCT), J3.5 (RCT), R10.2
U4_TOCAP: C15.1, U4.20 (TOCAP)
U4_VREG12: C16.1, U4.22 (1V2O)
U4_XI: C13.1, R6.1, U4.30 (XI/CLKIN), Y1.1
U4_XO: C14.1, R6.2, U4.31 (XO), Y1.3
USB_DM: J2.A7 (D-), J2.B7 (D-), U2.3 (I/O2), U2.4 (I/O2), U3.13 (USB_D-)
USB_DP: J2.A6 (D+), J2.B6 (D+), U2.1 (I/O1), U2.6 (I/O1), U3.14 (USB_D+)
VBUS: C9.1, D3.2 (A), J2.A4 (VBUS), J2.A9 (VBUS), J2.B4 (VBUS), J2.B9 (VBUS), U2.5 (VBUS)
VIN: C1.1, C2.1, C3.1, D1.1 (K), D2.1 (A1), D3.1 (K), U1.2 (VIN), U1.3 (EN)
VIN_RAW: D1.2 (A), J1.1

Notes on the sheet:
9-36 V in -> LMR36510 -> 3.3 V (USB OR-ed in)
USB-C: 5 V in + USB 2.0 data
USB ESD clamp
ESP32-S3-WROOM-1 (native USB)
W5500 Ethernet + HR911105A MagJack
CAN (SN65HVD230) + switchable 120 R
Isolated RS-485 (ADM2587E) + switchable 120 R
BOOT button (IO0)
RESET button (EN)
3V3 power LED
RUN LED (IO14)
ERR LED (IO21)
M3 hole, top left
M3 hole, top right
M3 hole, bottom left
M3 hole, bottom right
Power flags

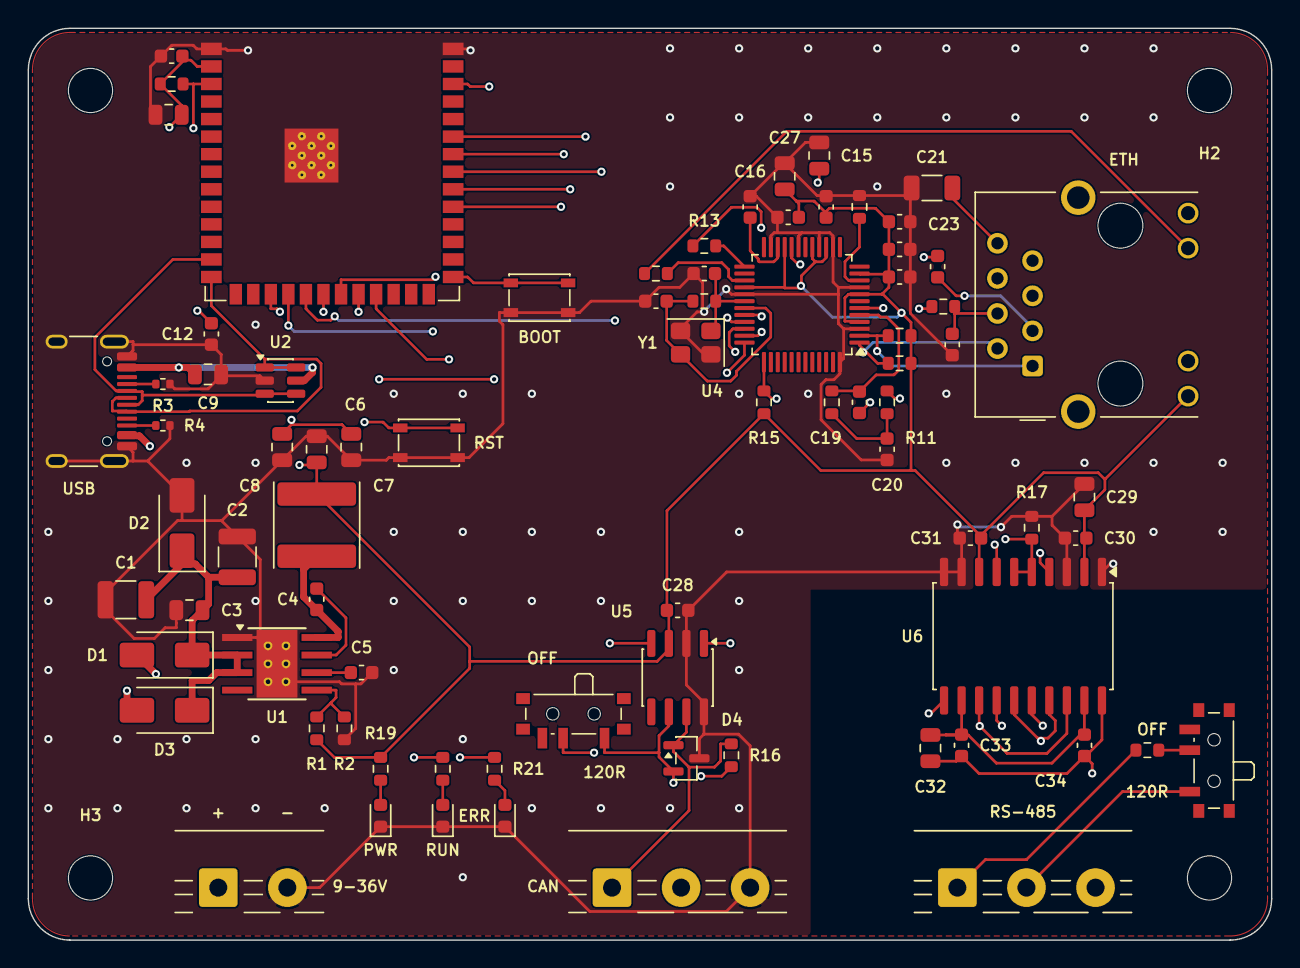
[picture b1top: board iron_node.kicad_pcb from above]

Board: 4 copper layers, 90.0 x 66.0 mm, 83 parts (0 on the bottom side), 57 nets.

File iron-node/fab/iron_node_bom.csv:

"Reference","Value","Footprint","MPN","LCSC","Qty"
"C1,C2","2.2uF","Capacitor_SMD:C_1210_3225Metric","FS32X225K101EGG","C153036","2"
"C3","100nF","Capacitor_SMD:C_0805_2012Metric","CL21B104KCFNNNE","C28233","1"
"C4,C10,C22,C23,C24,C25,C26,C28,C30,C31,C33,C34","100nF","Capacitor_SMD:C_0603_1608Metric","CC0603KRX7R9BB104","C14663","12"
"C5,C12","1uF","Capacitor_SMD:C_0603_1608Metric","CL10A105KB8NNNC","C15849","2"
"C6,C7,C8,C11","22uF","Capacitor_SMD:C_0805_2012Metric","CL21A226MAQNNNE","C45783","4"
"C9,C27,C29,C32","10uF","Capacitor_SMD:C_0805_2012Metric","CL21A106KAYNNNE","C15850","4"
"C13,C14","18pF","Capacitor_SMD:C_0603_1608Metric","CL10C180JB8NNNC","C1647","2"
"C15","4.7uF","Capacitor_SMD:C_0805_2012Metric","CL21A475KAQNNNE","C1779","1"
"C16,C20","10nF","Capacitor_SMD:C_0603_1608Metric","0603B103K500NT","C57112","2"
"C17","22nF","Capacitor_SMD:C_0603_1608Metric","CL10B223KB8NNNC","C21122","1"
"C18,C19","6.8nF","Capacitor_SMD:C_0603_1608Metric","0603B682K500NT","C1631","2"
"C21","1nF","Capacitor_SMD:C_1206_3216Metric","1206B102K202NT","C9196","1"
"D1,D3","SS36","Diode_SMD:D_SMA","SS36","C16015","2"
"D2","SMAJ36A","Diode_SMD:D_SMA","SMAJ36A","C113967","1"
"D4","NUP2105L","Package_TO_SOT_SMD:SOT-23","NUP2105LT1G","C14486","1"
"D5","Red (PWR)","LED_SMD:LED_0603_1608Metric","KT-0603R","C2286","1"
"D6","Orange (RUN)","LED_SMD:LED_0603_1608Metric","XL-1608UOC-06","C965800","1"
"D7","Red (ERR)","LED_SMD:LED_0603_1608Metric","KT-0603R","C2286","1"
"J1","9-36V IN","TerminalBlock:TerminalBlock_MaiXu_MX126-5.0-02P_1x02_P5.00mm","MX126-5.0-02P-GN01-Cu-S-A","C5188434","1"
"J2","USB-C","Connector_USB:USB_C_Receptacle_HRO_TYPE-C-31-M-12","TYPE-C-31-M-12","C165948","1"
"J3","HR911105A","Connector_RJ:RJ45_Hanrun_HR911105A_Horizontal","HR911105A","C12074","1"
"J4","CAN","TerminalBlock:TerminalBlock_MaiXu_MX126-5.0-03P_1x03_P5.00mm","MX126-5.0-03P-GN01-Cu-S-A","C5188435","1"
"J5","RS-485","TerminalBlock:TerminalBlock_MaiXu_MX126-5.0-03P_1x03_P5.00mm","MX126-5.0-03P-GN01-Cu-S-A","C5188435","1"
"L1","22uH","Inductor_SMD:L_Sunlord_SWPA6045S","SWPA6045S220MT","C83454","1"
"R1","47k","Resistor_SMD:R_0603_1608Metric","0603WAF4702T5E","C25819","1"
"R2","20k","Resistor_SMD:R_0603_1608Metric","0603WAF2002T5E","C4184","1"
"R3,R4","5.1k","Resistor_SMD:R_0402_1005Metric","0402WGF5101TCE","C25905","2"
"R5,R15,R17","10k","Resistor_SMD:R_0603_1608Metric","0603WAF1002T5E","C25804","3"
"R6","1M","Resistor_SMD:R_0603_1608Metric","0603WAF1004T5E","C22935","1"
"R7","12.4k","Resistor_SMD:R_0603_1608Metric","FRC0603F1242TS","C2930060","1"
"R8,R9,R11,R12","49.9","Resistor_SMD:R_0603_1608Metric","0603WAF499JT5E","C23185","4"
"R10","10","Resistor_SMD:R_0603_1608Metric","0603WAF100JT5E","C22859","1"
"R13,R14","330","Resistor_SMD:R_0603_1608Metric","0603WAF3300T5E","C23138","2"
"R16,R18","120","Resistor_SMD:R_0603_1608Metric","0603WAF1200T5E","C22787","2"
"R19,R20,R21","1k","Resistor_SMD:R_0603_1608Metric","0603WAF1001T5E","C21190","3"
"SW1,SW2","PCM12","Button_Switch_SMD:SW_SPDT_PCM12","PCM12SMTR","C221841","2"
"SW3","BOOT","Button_Switch_SMD:SW_SPST_PTS810","PTS810SJM250SMTRLFS","C116501","1"
"SW4","RESET","Button_Switch_SMD:SW_SPST_PTS810","PTS810SJM250SMTRLFS","C116501","1"
"U1","LMR36510ADDAR","Package_SO:Texas_HTSOP-8-1EP_3.9x4.9mm_P1.27mm_EP2.95x4.9mm_Mask2.4x3.1mm_ThermalVias","LMR36510ADDAR","C1858393","1"
"U2","USBLC6-2SC6","Package_TO_SOT_SMD:SOT-23-6","USBLC6-2SC6","C7519","1"
"U3","ESP32-S3-WROOM-1-N8R8","RF_Module:ESP32-S3-WROOM-1","ESP32-S3-WROOM-1-N8R8","C2913201","1"
"U4","W5500","Package_QFP:LQFP-48_7x7mm_P0.5mm","W5500","C32843","1"
"U5","SN65HVD230DR","Package_SO:SOIC-8_3.9x4.9mm_P1.27mm","SN65HVD230DR","C12084","1"
"U6","ADM2587EBRWZ","Package_SO:SOIC-20W_7.5x12.8mm_P1.27mm","ADM2587EBRWZ-REEL7","C12081","1"
"Y1","25MHz","Crystal:Crystal_SMD_3225-4Pin_3.2x2.5mm","X322525MOB4SI","C9006","1"
